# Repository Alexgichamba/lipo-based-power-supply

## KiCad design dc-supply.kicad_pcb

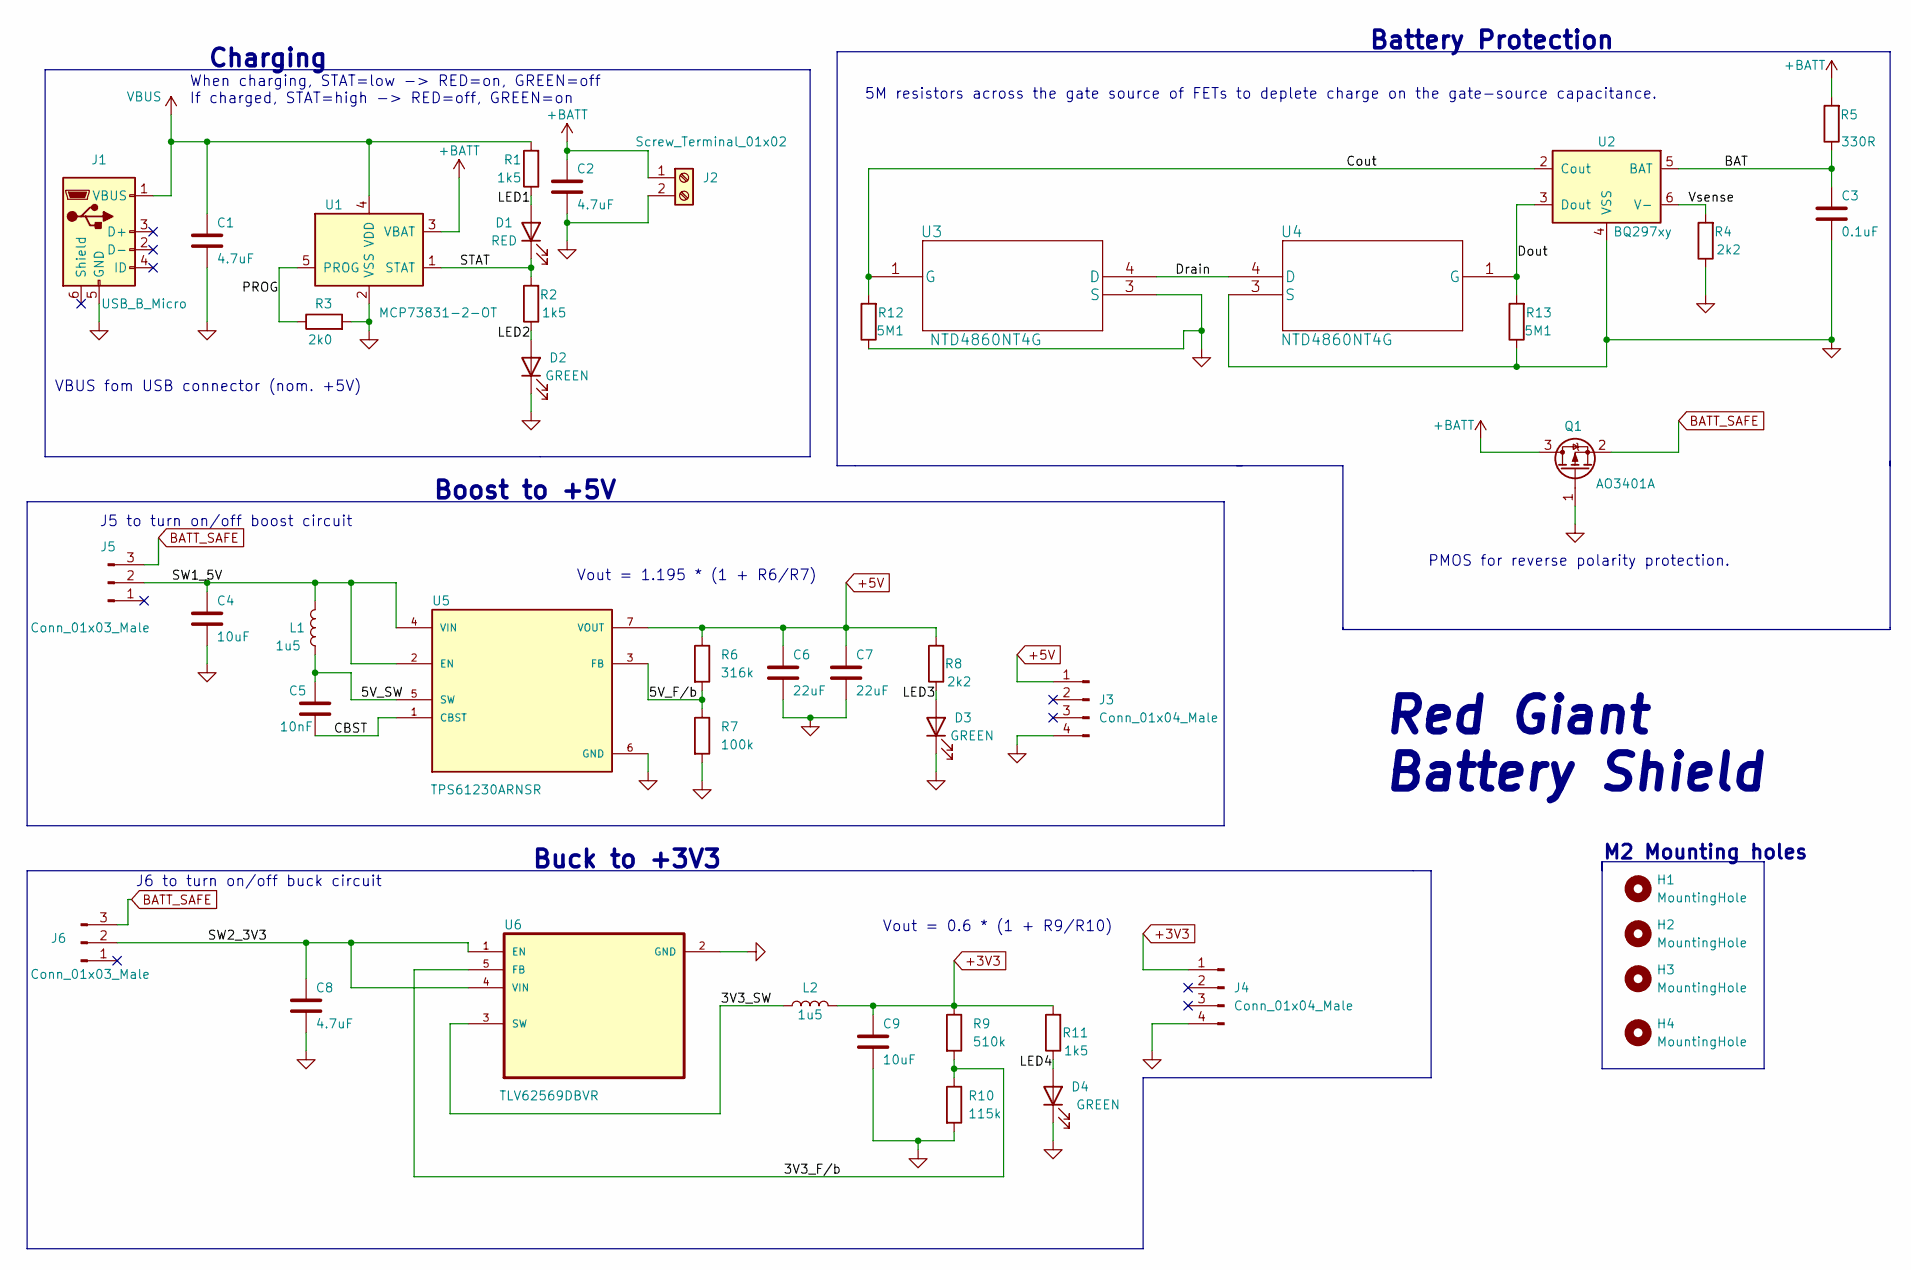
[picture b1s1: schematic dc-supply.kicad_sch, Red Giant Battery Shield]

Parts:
C1, C2: 4.7uF; C_0603_1608Metric
C3: 0.1uF; C_0402_1005Metric
C4, C9: 10uF; C_0805_2012Metric
C5: 10nF; C_0603_1608Metric
C6, C7: 22uF; C_0805_2012Metric
C8: 4.7uF; C_0805_2012Metric
D1: RED; LED_0603_1608Metric
D2, D3, D4: GREEN; LED_0603_1608Metric
H1, H2, H3, H4: MountingHole; MountingHole_2.2mm_M2
J1: USB_B_Micro; USB_Micro-B_Wuerth_629105150521
J2: Screw_Terminal_01x02; TerminalBlock_bornier-2_P5.08mm
J3, J4: Conn_01x04_Male; PinHeader_1x04_P2.54mm_Vertical
J5, J6: Conn_01x03_Male; PinHeader_1x03_P2.54mm_Vertical
L1, L2: 1u5; SWPA3015S1R5NT
Q1: AO3401A; SOT-23
R1, R2, R11: 1k5; R_0402_1005Metric
R3: 2k0; R_0402_1005Metric
R4, R8: 2k2; R_0402_1005Metric
R5: 330R; R_0805_2012Metric
R6: 316k; R_0603_1608Metric
R7: 100k; R_0603_1608Metric
R9: 510k; R_0603_1608Metric
R10: 115k; R_0603_1608Metric
R12, R13: 5M1; R_0603_1608Metric
U1: MCP73831-2-OT; SOT-23-5
U2: BQ297xy; WSON-6_1.5x1.5mm_P0.5mm
U3, U4: NTD4860NT4G; DPAK229P990X238-4N
U5: TPS61230ARNSR; IC_TPS61230ARNSR; PARTREV B
U6: TLV62569DBVR; SOT95P280X145-5N

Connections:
+3V3: C9.1, J4.1, L2.2, R9.1, R11.2
+5V: C6.1, C7.1, J3.1, R6.1, R8.2, U5.7 (VOUT)
+BATT: C2.1, J2.1, Q1.3 (D), R5.2, U1.3 (VBAT)
/3V3_F/b: R9.2, R10.1, U6.5 (FB)
/3V3_SW: L2.1, U6.3 (SW)
/5V_F/b: R6.2, R7.1, U5.3 (FB)
/5V_SW: C5.1, L1.1, U5.5 (SW)
/BAT: C3.1, R5.1, U2.5 (BAT)
/CBST: C5.2, U5.1 (CBST)
/Cout: R12.2, U2.2 (Cout), U3.1 (G)
/Dout: R13.2, U2.3 (Dout), U4.1 (G)
/Drain: U3.4 (D), U4.4 (D)
/LED1: D1.2 (A), R1.1
/LED2: D2.2 (A), R2.1
/LED3: D3.2 (A), R8.1
/LED4: D4.2 (A), R11.1
/PROG: R3.1, U1.5 (PROG)
/STAT: D1.1 (K), R2.2, U1.1 (STAT)
/SW1_5V: C4.1, J5.2, L1.2, U5.2 (EN), U5.4 (VIN)
/SW2_3V3: C8.1, J6.2, U6.1 (EN), U6.4 (VIN)
/Vsense: R4.2, U2.6 (V-)
BATT_SAFE: J5.3, J6.3, Q1.2 (S)
GND: C1.2, C2.2, C3.2, C4.2, C6.2, C7.2, C8.2, C9.2, D2.1 (K), D3.1 (K), D4.1 (K), J1.5 (GND), J2.2, J3.4, J4.4, Q1.1 (G), R3.2, R4.1, R7.2, R10.2, R12.1, R13.1, U1.2 (VSS), U2.4 (VSS), U3.3 (S), U4.3 (S), U5.6 (GND), U6.2 (GND)
VBUS: C1.1, J1.1 (VBUS), R1.2, U1.4 (VDD)

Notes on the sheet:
M2 Mounting holes
Vout = 0.6 * (1 + R9/R10)
Vout = 1.195 * (1 + R6/R7)
PMOS for reverse polarity protection.
Buck to +3V3
J6 to turn on/off buck circuit
Battery Protection
Red Giant Battery Shield
VBUS fom USB connector (nom. +5V)
Boost to +5V
Charging
When charging, STAT=low -> RED=on, GREEN=off If charged, STAT=high -> RED=off, GREEN=on
5M resistors across the gate source of FETs to deplete charge on the gate-source capacitance.
J5 to turn on/off boost circuit

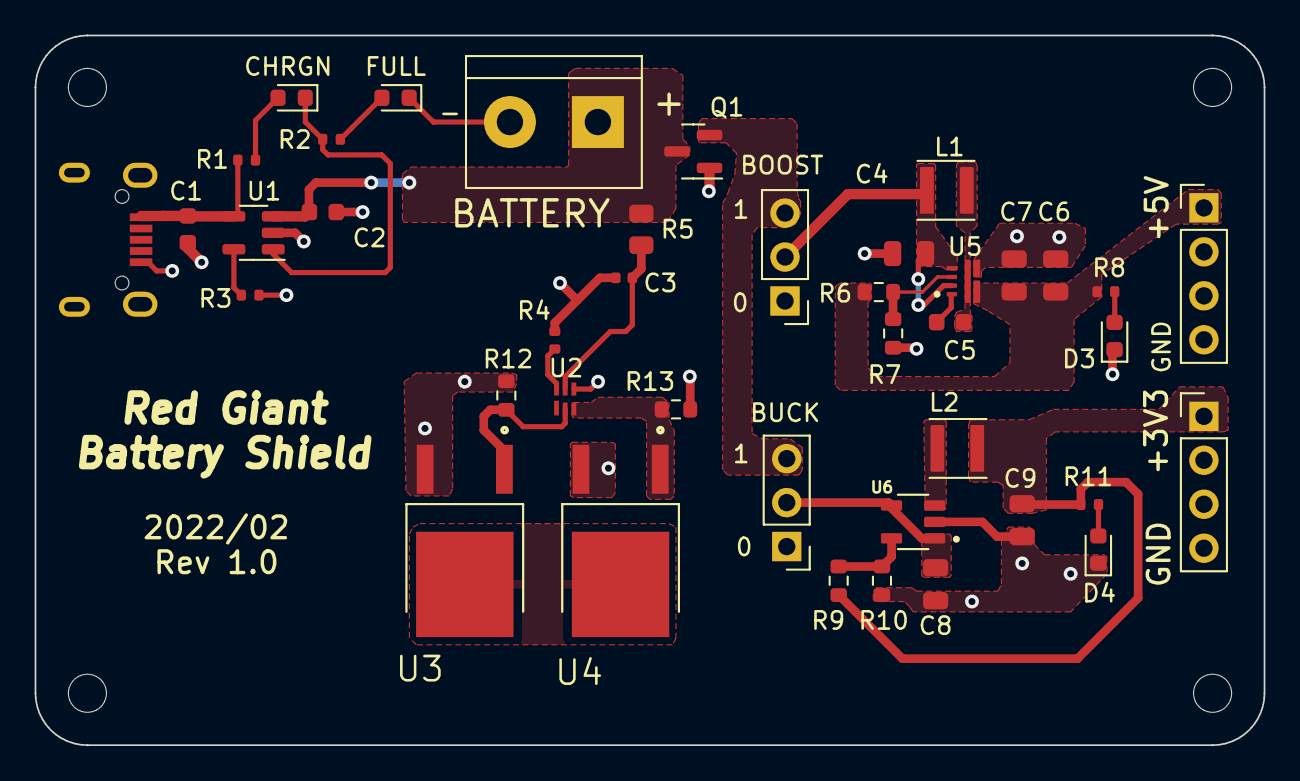
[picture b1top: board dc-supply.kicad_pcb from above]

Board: 2 copper layers, 71.0 x 41.0 mm, 45 parts (0 on the bottom side), 24 nets.

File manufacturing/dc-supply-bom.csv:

Comment,Designator,Footprint,LCSC
4.7uF,"C1,C2",Capacitor_SMD:C_0603_1608Metric,C389010
0.1uF,C3,Capacitor_SMD:C_0402_1005Metric,C60474
10uF,"C4,C9",Capacitor_SMD:C_0805_2012Metric,C117956
10nF,C5,Capacitor_SMD:C_0603_1608Metric,C100042
22uF,"C6,C7",Capacitor_SMD:C_0805_2012Metric,C77074
4.7uF,C8,Capacitor_SMD:C_0805_2012Metric,C415536
RED,D1,LED_SMD:LED_0603_1608Metric,C72044
GREEN,"D2,D3,D4",LED_SMD:LED_0603_1608Metric,C434423
MountingHole,"H1,H2,H3,H4",MountingHole:MountingHole_2.2mm_M2,
USB_B_Micro,J1,Connector_USB:USB_Micro-B_Wuerth_629105150521,
Screw_Terminal_01x02,J2,TerminalBlock:TerminalBlock_bornier-2_P5.08mm,
Conn_01x04_Male,"J3,J4",Connector_PinHeader_2.54mm:PinHeader_1x04_P2.54mm_Vertical,
Conn_01x03_Male,"J5,J6",Connector_PinHeader_2.54mm:PinHeader_1x03_P2.54mm_Vertical,
1u5,"L1,L2",SWPA3015S1R5NT:SWPA3015S1R5NT,
AO3401A,Q1,Package_TO_SOT_SMD:SOT-23,C347476
1k5,"R1,R2,R11",Resistor_SMD:R_0402_1005Metric,C144792
115k,R10,Resistor_SMD:R_0603_1608Metric,C22783
5M1,"R12,R13",Resistor_SMD:R_0603_1608Metric,C141664
2k0,R3,Resistor_SMD:R_0402_1005Metric,C351699
2k2,"R4,R8",Resistor_SMD:R_0402_1005Metric,C114762
330R,R5,Resistor_SMD:R_0805_2012Metric,C17630
316k,R6,Resistor_SMD:R_0603_1608Metric,C227814
100k,R7,Resistor_SMD:R_0603_1608Metric,C25803
510k,R9,Resistor_SMD:R_0603_1608Metric,C23192
MCP73831-2-OT,U1,Package_TO_SOT_SMD:SOT-23-5,C14879
BQ297xy,U2,Package_SON:WSON-6_1.5x1.5mm_P0.5mm,C183096
NTD4860NT4G,"U3,U4",DPAK229P990X238-4N:DPAK229P990X238-4N,C242292
TPS61230ARNSR,U5,TPS61230ARNSR:IC_TPS61230ARNSR,C376005
TLV62569DBVR,U6,MCP73831T-2ATI_OT:SOT95P280X145-5N,C141836

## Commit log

2022-03-04 initial commit
    added the design, manufacturing and simulation files.
